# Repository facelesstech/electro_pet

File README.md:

# electro_pet
Electro pet based on the petduino with a few more bells and whistles

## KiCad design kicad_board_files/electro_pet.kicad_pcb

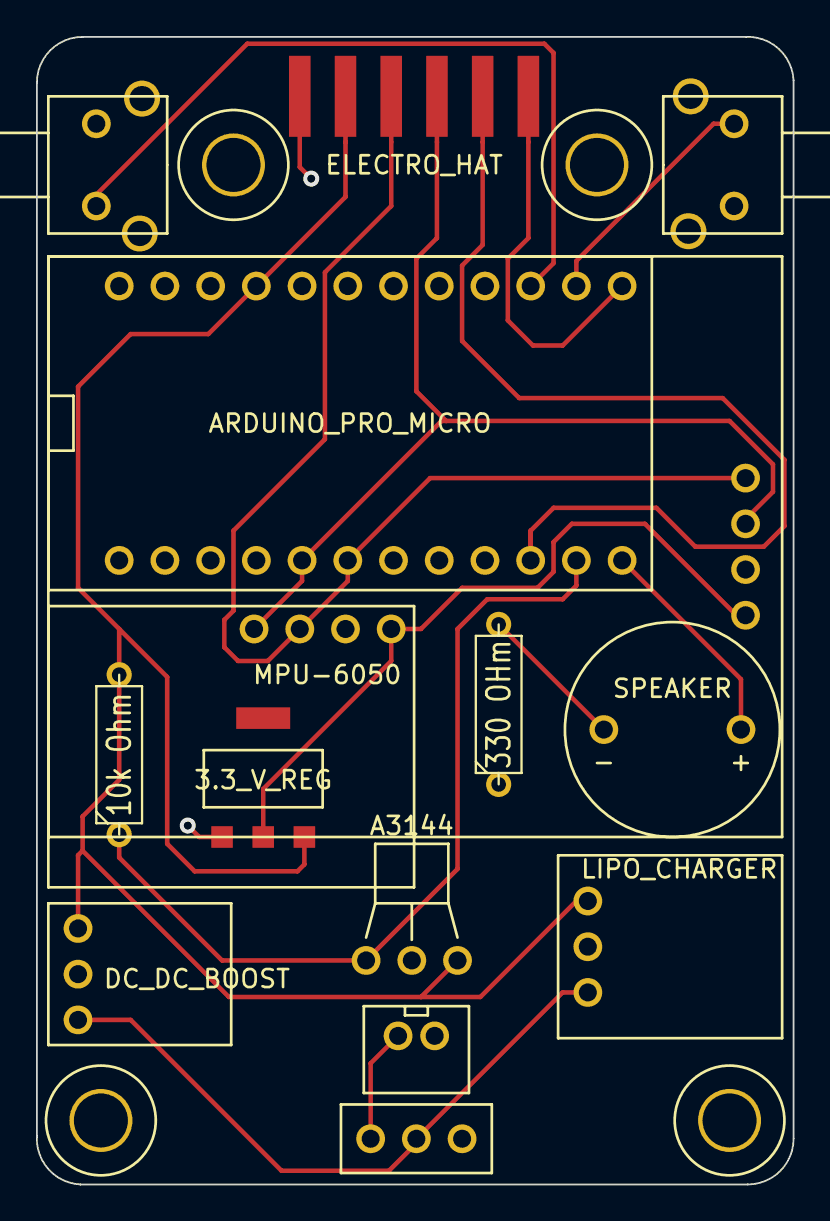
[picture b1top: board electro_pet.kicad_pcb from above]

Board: 2 copper layers, 42.0 x 63.8 mm, 20 parts (0 on the bottom side), 14 nets.

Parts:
10k Ohm, 330 OHm: R; R3-5
M3_bolt_nut_custom, M3_bolt_nut_custom#2, M3_bolt_nut_custom#3, M3_bolt_nut_custom#4: VAL**; M3_bolt_nut_custom
SP1: SPEAKER; piezo_small_custom
SW1: SWITCH_INV; 3_pin_switch_custom
SW2, SW3: SW_PUSH; right_angle_button_custom
U1: 8X8_LED_MATRIX; 8x8_matrix_custom
U2: LIPO_CHARGER; small_lipo_charger
U3: ELECTRO_HAT; electro_hat_custom
U4: 3.3_V_REG; AMS1117_custom
U5: MPU-6050; mpu-6050_custom
U6: DC_DC_BOOST; small_DC_DC_boost
U7: ARDUINO_PRO_MICRO; arduino_leonardo
U8: BATTERY_CUSTOM; JST-PH_custom
U9: A3144; A3144_custom
VAL: OSH_final_silks_back

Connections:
unnamed: 330 OHm.1, SW2.2, SW3.2, U1.3, U2.2, U3.1, U4.1, U5.2, U6.2, U7.23, U8.1, U9.2
unnamed: SW1.1, U8.2
unnamed: U3.5, U7.10
unnamed: SW2.1, U7.15
unnamed: U3.6, U7.13
unnamed: U1.1, U3.3, U5.3, U7.6
unnamed: U1.2, U3.4, U5.4, U7.5
unnamed: SW3.1, U7.14
unnamed: 10k Ohm.2, U2.1, U3.2, U4.3, U6.1, U7.21, U9.1
unnamed: 330 OHm.2, SP1.1
unnamed: SP1.2, U7.12
unnamed: SW1.2, U2.3, U6.3
unnamed: U1.4, U4.2, U5.1
unnamed: 10k Ohm.1, U7.11, U9.3

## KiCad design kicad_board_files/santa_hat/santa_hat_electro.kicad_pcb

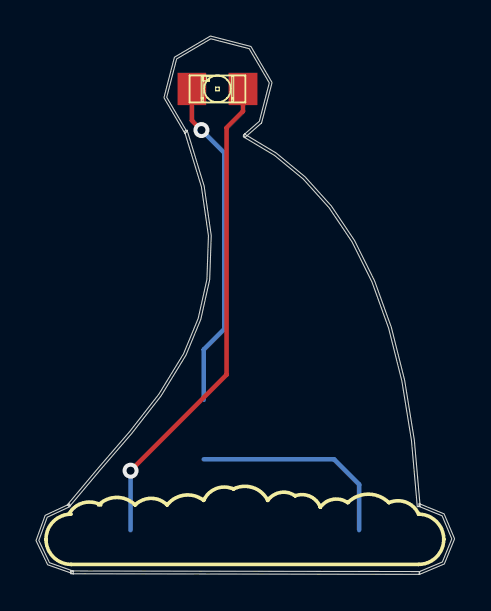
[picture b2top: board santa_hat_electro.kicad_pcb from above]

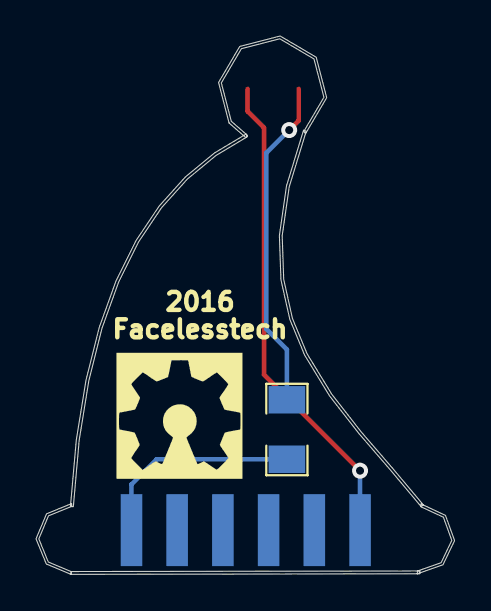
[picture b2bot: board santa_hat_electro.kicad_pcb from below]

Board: 2 copper layers, 23.3 x 29.9 mm, 5 parts (2 on the bottom side), 3 nets.

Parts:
D1: LED; LED-1206
R1: R; SM1206
U1: ELECTRO_HAT; electro_hat_male_mirrored
VAL: OSH_final_silks_back
svg2mod: Edge.Cuts; svg2mod

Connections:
unnamed: R1.1, U1.1
unnamed: D1.2, R1.2
unnamed: D1.1, U1.6

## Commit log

2016-09-27 Kicad board files and gerber files
2016-09-28 test code for all the modules
2016-10-17 fixed a wiring issue with the switch
2016-10-26 changed the folder name
2016-10-26 moved folder
2016-10-26 Santa hat for the pet
2016-11-11 New updated gerbers with all the battery changes
2016-11-11 Added the fixes for the battery
2016-11-16 Inkscape files for the laser cut acrylic
2016-11-16 fliped the header to the currect way
2016-11-23 reversed the santa hat so it will work this time around
2016-11-23 deleted files
2016-11-23 Final files that fixed the battery issue
2016-11-23 Breathalyzer hat with the MQ-3 sensor
2016-12-01 Arduino code for electro pet
2016-12-06 first upload of the breathalzer code for electro pet
2016-12-06 Shake the electro pet to roll the dice
2016-12-10 more sketches
2016-12-12 Added pin layout to the top of the files
2016-12-12 Snow globe skretch for electro pet
2016-12-17 Added santa hat code
2017-02-27 Added schmatics
